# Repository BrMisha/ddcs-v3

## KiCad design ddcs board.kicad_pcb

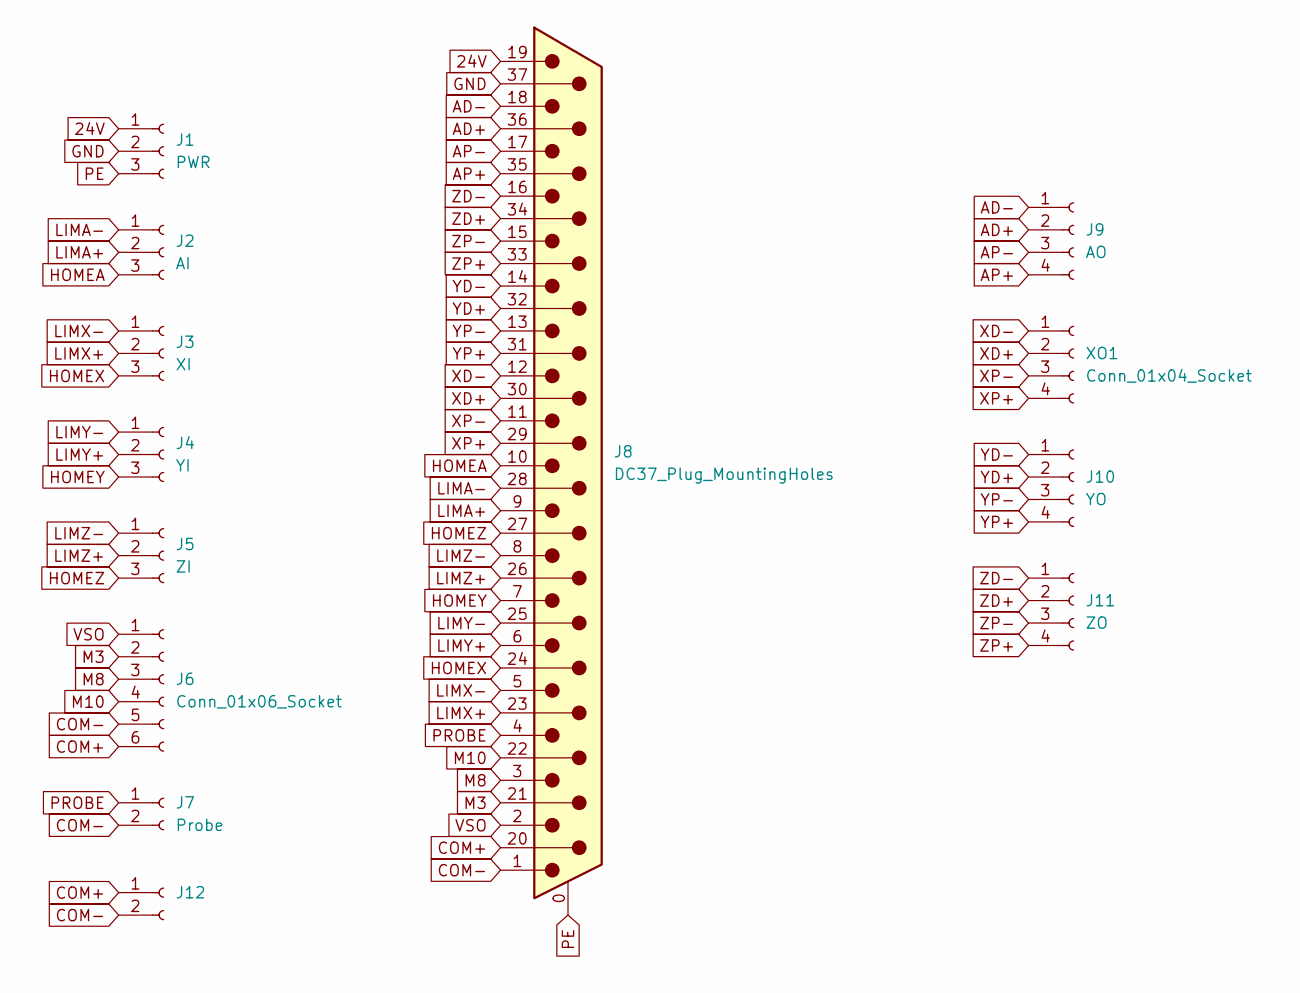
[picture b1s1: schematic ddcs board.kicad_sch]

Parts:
J1: PWR; TerminalBlock_bornier-3_P5.08mm
J2: AI; TerminalBlock_bornier-3_P5.08mm
J3: XI; TerminalBlock_bornier-3_P5.08mm
J4: YI; TerminalBlock_bornier-3_P5.08mm
J5: ZI; TerminalBlock_bornier-3_P5.08mm
J6: Conn_01x06_Socket; TerminalBlock_bornier-6_P5.08mm
J7: Probe; TerminalBlock_bornier-2_P5.08mm
J8: DC37_Plug_MountingHoles; DSUB-37_Male_Vertical_P2.77x2.84mm_MountingHoles
J9: AO; TerminalBlock_bornier-4_P5.08mm
J10: YO; TerminalBlock_bornier-4_P5.08mm
J11: ZO; TerminalBlock_bornier-4_P5.08mm
J12: TerminalBlock_bornier-2_P5.08mm
XO1: Conn_01x04_Socket; TerminalBlock_bornier-4_P5.08mm

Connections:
24V: J1.1, J8.19
AD+: J8.36, J9.2
AD-: J8.18, J9.1
AP+: J8.35, J9.4
AP-: J8.17, J9.3
COM+: J6.6, J8.20, J12.1
COM-: J6.5, J7.2, J8.1, J12.2
GND: J1.2, J8.37
HOMEA: J2.3, J8.10
HOMEX: J3.3, J8.24
HOMEY: J4.3, J8.7
HOMEZ: J5.3, J8.27
LIMA+: J2.2, J8.9
LIMA-: J2.1, J8.28
LIMX+: J3.2, J8.23
LIMX-: J3.1, J8.5
LIMY+: J4.2, J8.6
LIMY-: J4.1, J8.25
LIMZ+: J5.2, J8.26
LIMZ-: J5.1, J8.8
M3: J6.2, J8.21
M8: J6.3, J8.3
M10: J6.4, J8.22
PE: J1.3, J8.0 (PAD)
PROBE: J7.1, J8.4
VSO: J6.1, J8.2
XD+: J8.30, XO1.2
XD-: J8.12, XO1.1
XP+: J8.29, XO1.4
XP-: J8.11, XO1.3
YD+: J8.32, J10.2
YD-: J8.14, J10.1
YP+: J8.31, J10.4
YP-: J8.13, J10.3
ZD+: J8.34, J11.2
ZD-: J8.16, J11.1
ZP+: J8.33, J11.4
ZP-: J8.15, J11.3

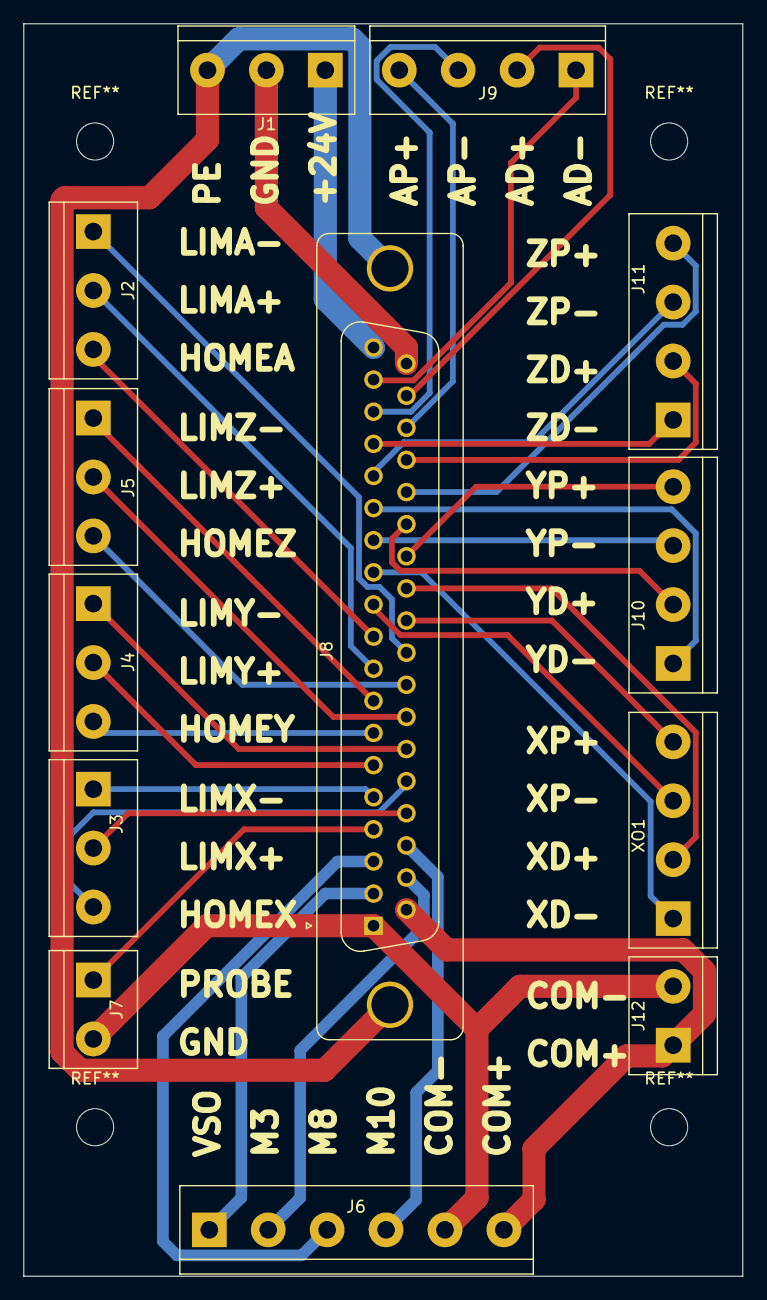
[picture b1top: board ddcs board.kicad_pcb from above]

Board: 2 copper layers, 62.0 x 108.0 mm, 13 parts (0 on the bottom side), 38 nets.
